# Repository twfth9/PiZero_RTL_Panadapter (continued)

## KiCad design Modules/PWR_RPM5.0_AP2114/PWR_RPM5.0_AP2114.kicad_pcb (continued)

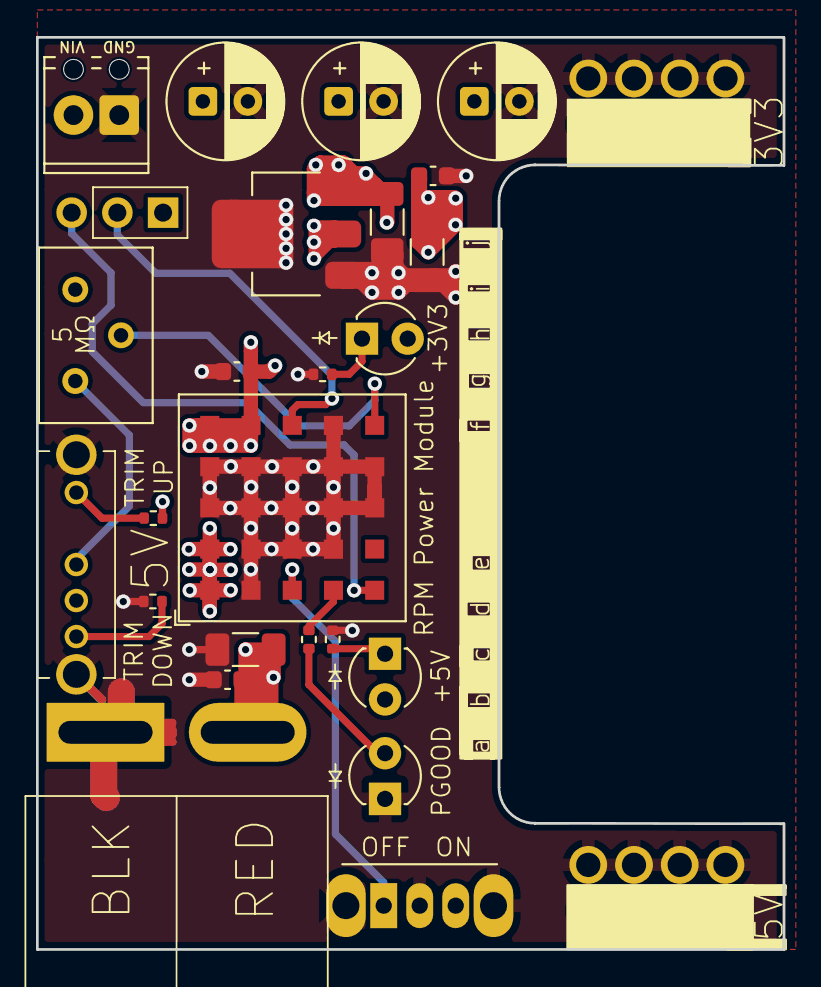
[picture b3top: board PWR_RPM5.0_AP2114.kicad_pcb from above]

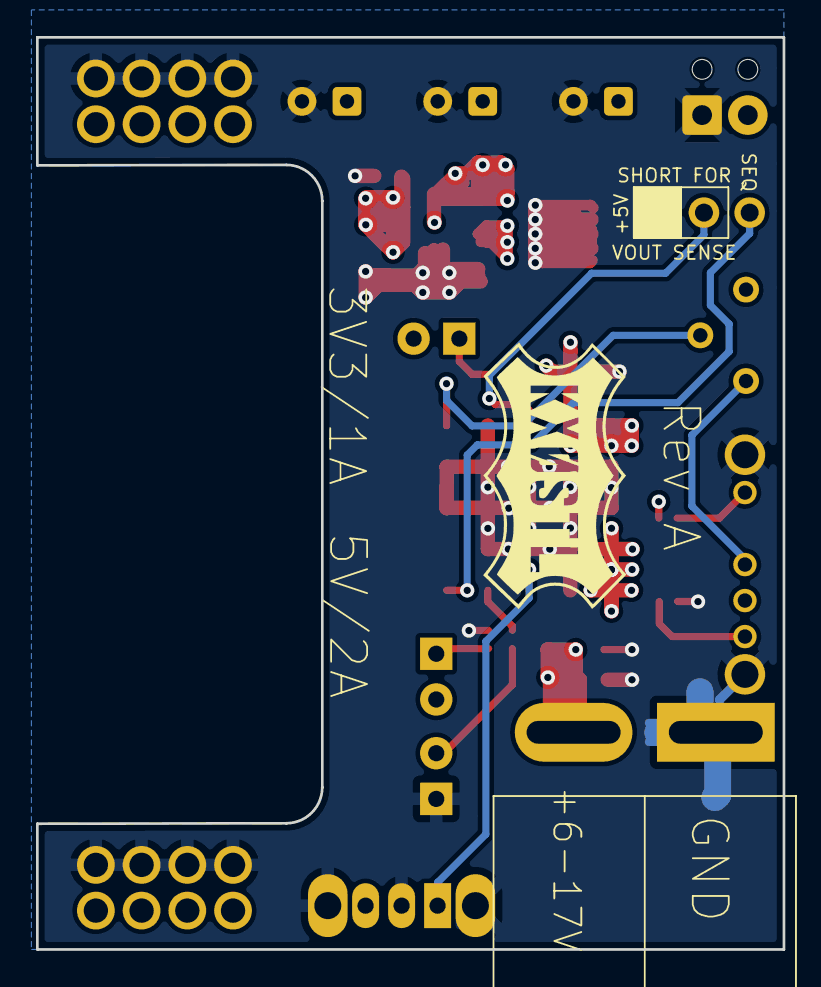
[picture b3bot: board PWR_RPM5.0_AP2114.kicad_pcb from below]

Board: 4 copper layers, 41.5 x 50.7 mm, 29 parts (3 on the bottom side), 15 nets.

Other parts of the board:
J8#2: Red/Black PowerPole 45; APP_ASMPR45-1X2-RK
